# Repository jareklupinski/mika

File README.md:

# mika
Part ESP8266 dev board, part thought experiment

Designed as a boilerplate for connecting legacy devices to the Internet of Things.

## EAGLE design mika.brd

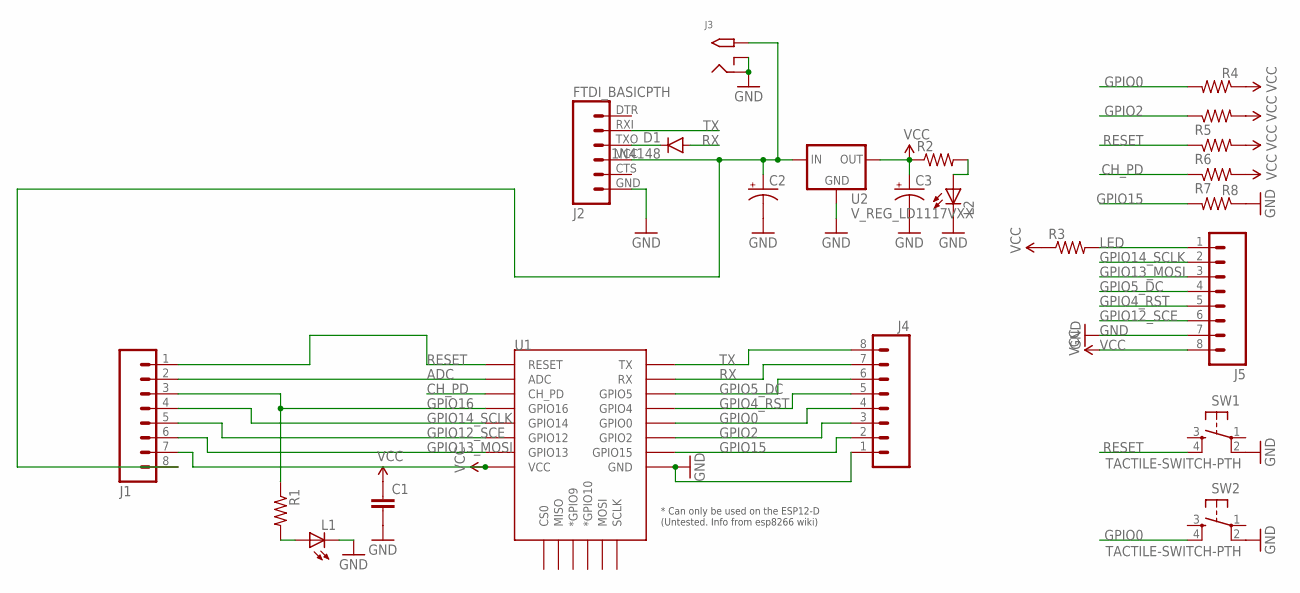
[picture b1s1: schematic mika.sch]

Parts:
C1: CAPKIT; CAP-PTH-SMALL-KIT
C2, C3: CAP_POLPTH2; CPOL-RADIAL-10UF-25V
D1: 1N4148; DIODE-1N4148
J1, J4: M083.5MM-8; SCREWTERMINAL-3.5MM-8
J2: FTDI_BASICPTH; FTDI_BASIC
J3: 2.1MMJACKTHM; PJ-102A
J5: M08; 1X08_ROUND
L1, L2: LED5MM
R1, R2, R3, R4, R5, R6, R7, R8: RESISTORKIT; AXIAL-0.3-KIT
SW1, SW2: TACTILE-SWITCH-PTH; TAC-SWITCH-PTH
U1: ESP12ESMD; ESP12E-SMD
U2: V_REG_LD1117VXX; 78XXL

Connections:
ADC: J1.2, U1.ADC
CH_PD: R7.P$1 (1), U1.CH_PD
GND: C1.2, C2.2 (-), C3.2 (-), J2.GND (6), J3.RING, J3.RING_SW, J4.1, J5.7, L1.K (C), L2.K (C), R8.P$1 (1), SW1.2, SW2.2, U1.GND, U2.GND
GPIO0: J4.4, R4.P$2 (2), SW2.4, U1.GPIO0
GPIO2: J4.3, R5.P$1 (1), U1.GPIO2
GPIO4_RST: J4.5, J5.5, U1.GPIO4
GPIO5_DC: J4.6, J5.4, U1.GPIO5
GPIO12_SCE: J1.5, J5.6, U1.GPIO12
GPIO13_MOSI: J1.6, J5.3, U1.GPIO13
GPIO14_SCLK: J1.4, J5.2, U1.GPIO14
GPIO15: J4.2, R8.P$2 (2), U1.GPIO15
GPIO16: J1.3, R1.P$1 (1), U1.GPIO16
LED: J5.1, R3.P$2 (2)
unnamed: D1.C, J2.TXO (3)
unnamed: C2.1 (+), J1.8, J2.VCC (4), J3.TIP, U2.IN
unnamed: L2.A, R2.P$2 (2)
unnamed: L1.A, R1.P$2 (2)
RESET: J1.1, R6.P$1 (1), SW1.4, U1.RESET
RX: D1.A, J4.7, U1.RXD0 (RX)
TX: J2.RXI (2), J4.8, U1.TXD0 (TX)
VCC: C1.1, C3.1 (+), J1.7, J5.8, R2.P$1 (1), R3.P$1 (1), R4.P$1 (1), R5.P$2 (2), R6.P$2 (2), R7.P$2 (2), U1.VCC, U2.OUT

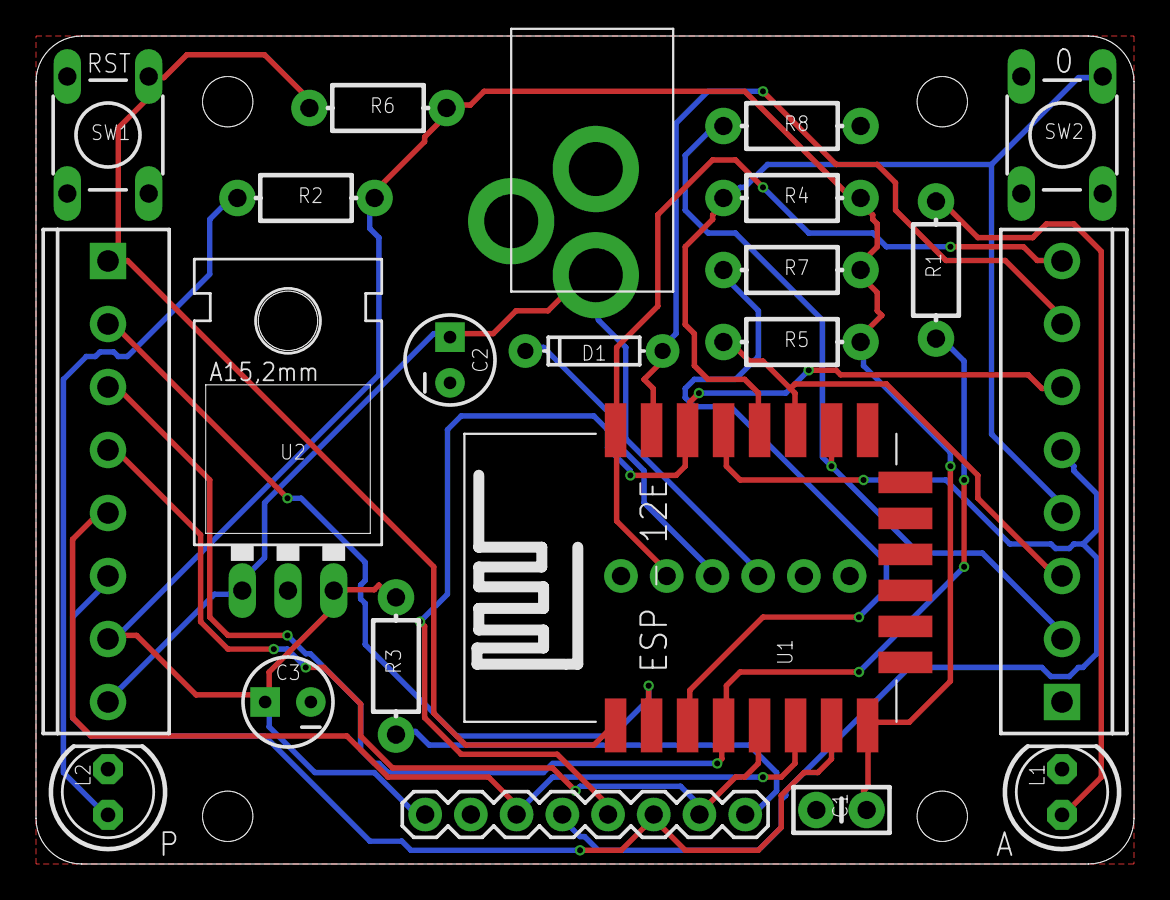
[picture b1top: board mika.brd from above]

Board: 2 copper layers, 61.0 x 46.0 mm, 23 parts (1 on the bottom side), 21 nets.

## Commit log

2018-07-06 design tested: working

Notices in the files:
parts and their libraries:
SparkFun-Capacitors: Licensing: Creative Commons ShareAlike 4.0 International - https://creativecommons.org/licenses/by-sa/4.0
